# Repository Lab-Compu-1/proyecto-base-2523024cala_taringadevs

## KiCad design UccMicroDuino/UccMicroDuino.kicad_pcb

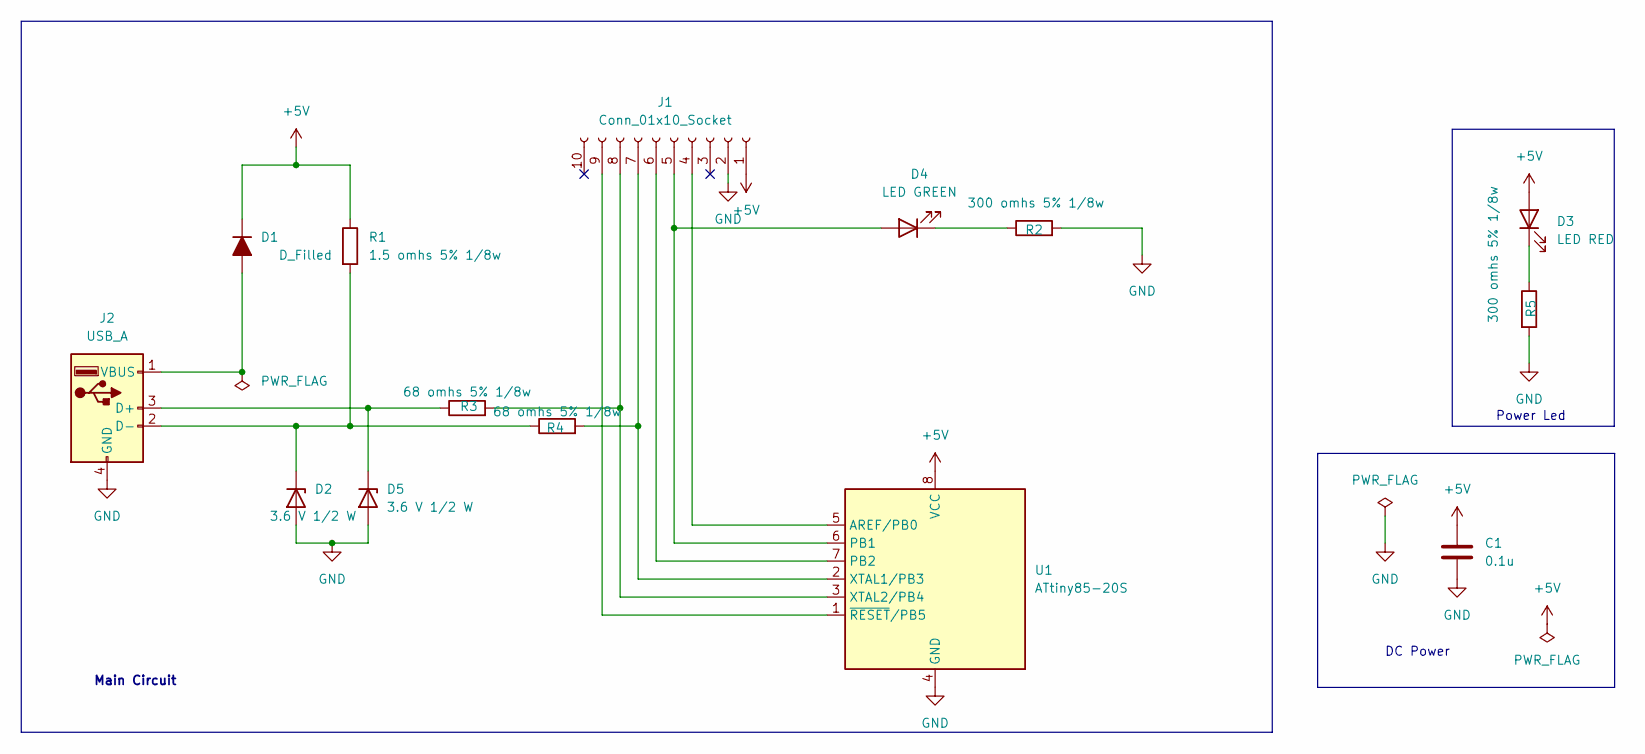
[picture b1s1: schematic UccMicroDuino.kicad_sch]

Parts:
C1: 0.1u; C_0805_2012Metric_Pad1.18x1.45mm_HandSolder
D1: D_Filled; D_MiniMELF
D2, D5: 3.6 V 1/2 W; D_SOD-123
D3: LED RED; ledSMD
D4: LED GREEN; ledSMD
J1: Conn_01x10_Socket; PinHeader_1x10_P2.54mm_Vertical
J2: USB_A; USB_A_UCC
R1: 1.5 omhs 5% 1/8w; R_0805_2012Metric_Pad1.20x1.40mm_HandSolder
R2, R5: 300 omhs 5% 1/8w; R_0805_2012Metric_Pad1.20x1.40mm_HandSolder
R3, R4: 68 omhs 5% 1/8w; R_0805_2012Metric_Pad1.20x1.40mm_HandSolder
U1: ATtiny85-20S; SOIC-8_5.3x5.3mm_P1.27mm

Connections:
+5V: C1.1, D1.1 (K), D3.2 (A), J1.1, R1.1, U1.8 (VCC)
GND: C1.2, D2.2 (A), D5.2 (A), J1.2, J2.4 (GND), R2.2, R5.2, U1.4 (GND)
unnamed: D1.2 (A), J2.1 (VBUS)
unnamed: D2.1 (K), J2.2 (D-), R1.2, R4.1
unnamed: D3.1 (K), R5.1
unnamed: D4.2 (A), J1.5, U1.6 (PB1)
unnamed: D4.1 (K), R2.1
unnamed: D5.1 (K), J2.3 (D+), R3.1
unnamed: J1.4, U1.5 (AREF/PB0)
unnamed: J1.6, U1.7 (PB2)
unnamed: J1.7, R4.2, U1.2 (XTAL1/PB3)
unnamed: J1.8, R3.2, U1.3 (XTAL2/PB4)
unnamed: J1.9, U1.1 (~RESET/PB5)

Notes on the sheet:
DC Power
Main Circuit
Power Led

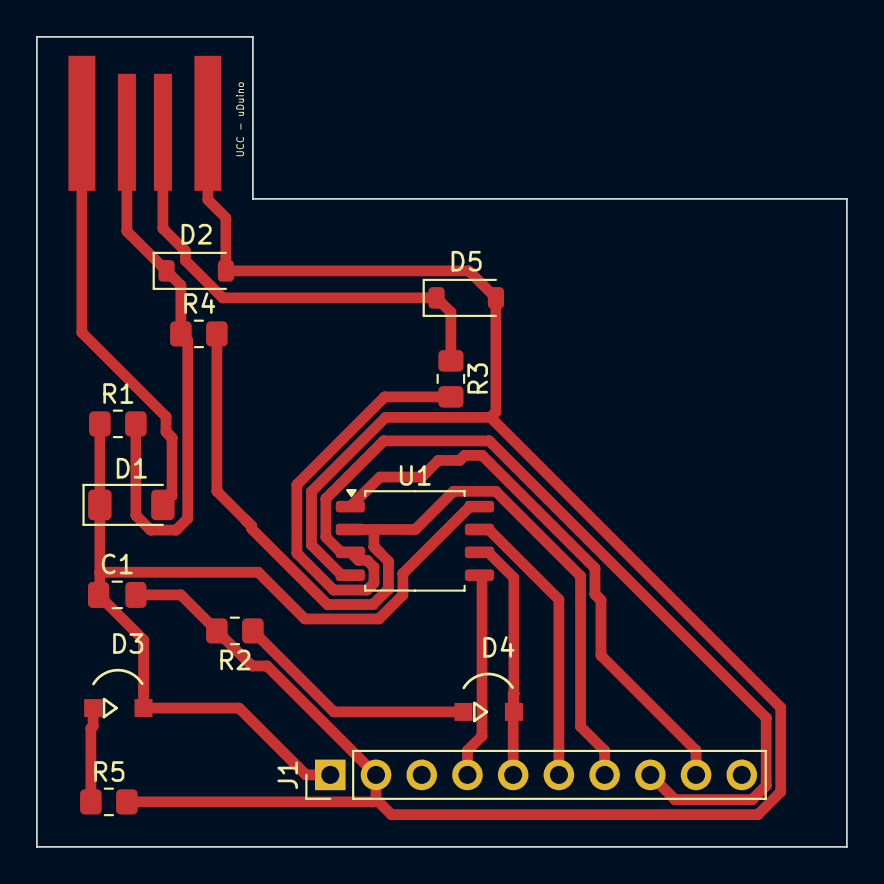
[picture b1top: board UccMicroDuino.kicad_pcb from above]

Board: 2 copper layers, 45.0 x 45.0 mm, 14 parts (0 on the bottom side), 13 nets.

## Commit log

2025-03-17 GitHub Classroom Feedback
2025-03-17 Setting up GitHub Classroom Feedback
2025-03-31 diseño de circuito en kicad
2025-03-31 Diseño de circuito en KiCad finalizado
2025-04-07 acomodacion de lineas
2025-04-28 arreglo
2025-05-05 clase 5 de mayo
2025-05-19 terminado
